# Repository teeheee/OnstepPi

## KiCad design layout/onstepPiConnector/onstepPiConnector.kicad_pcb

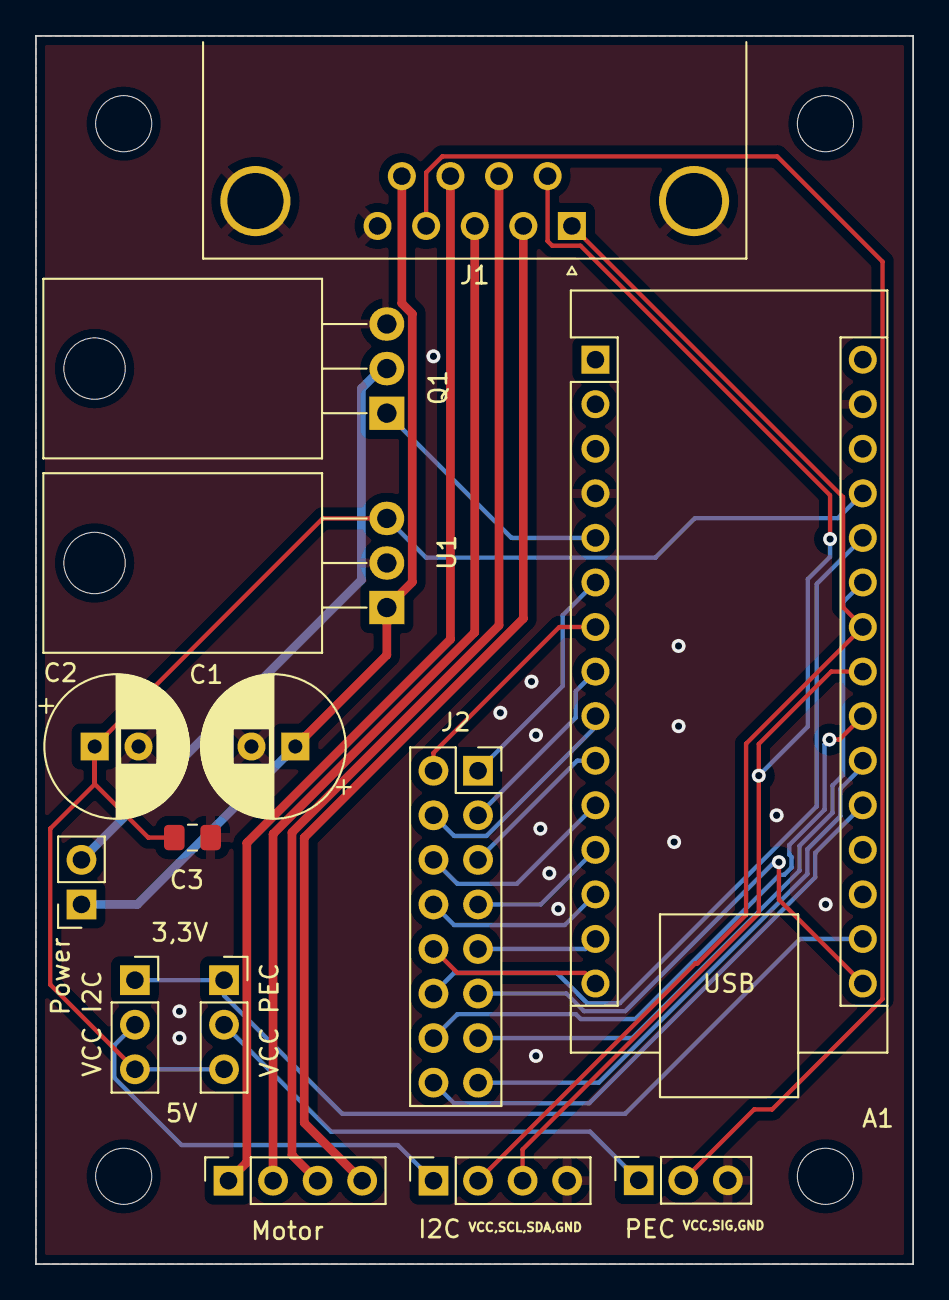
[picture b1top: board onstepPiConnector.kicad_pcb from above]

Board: 2 copper layers, 50.0 x 70.0 mm, 14 parts (0 on the bottom side), 31 nets.

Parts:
A1: Arduino_Nano_v3.x; Arduino_Nano
C1, C2: C_Polarized; CP_Radial_D8.0mm_P2.50mm
C3: C; C_0805_2012Metric_Pad1.18x1.45mm_HandSolder
I2C: Conn_01x04; PinSocket_1x04_P2.54mm_Vertical
J1: DB9_Male_MountingHoles; DSUB-9_Male_Horizontal_P2.77x2.84mm_EdgePinOffset7.70mm_Hou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
J2: Conn_01x16_Male; PinSocket_2x08_P2.54mm_Vertical
Motor: Conn_01x04; PinSocket_1x04_P2.54mm_Vertical
PEC: Conn_01x03; PinSocket_1x03_P2.54mm_Vertical
Power: Conn_01x02; PinSocket_1x02_P2.54mm_Vertical
Q1: IRF540N; TO-220-3_Horizontal_TabDown
U1: L7805; TO-220-3_Horizontal_TabDown
VCC I2C: Jumper_3_Open; PinSocket_1x03_P2.54mm_Vertical
VCC PEC: Jumper_3_Open; PinSocket_1x03_P2.54mm_Vertical

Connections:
+3.3V: A1.17 (3V3), VCC I2C.1 (A), VCC PEC.1 (A)
+5V: A1.27 (+5V), C2.1, C3.1, U1.3 (OUT), VCC I2C.3 (B), VCC PEC.3 (B)
+12V: C1.1, J1.9, Power.1, U1.1 (IN)
GND: A1.4 (GND), A1.29 (GND), C1.2, C2.2, C3.2, I2C.4, J1.0 (PAD), J1.5, PEC.3, Q1.3 (S), U1.2 (GND)
M1A: J1.3, Motor.2
M1B: J1.8, Motor.1
M2A: J1.7, Motor.3
M2B: J1.2, Motor.4
unnamed: A1.5 (D2), Q1.1 (G)
unnamed: A1.6 (D3), J2.1
unnamed: A1.7 (D4), J2.2
unnamed: A1.8 (D5), J2.3
unnamed: A1.9 (D6), J2.4
unnamed: A1.10 (D7), J2.5
unnamed: A1.11 (D8), J2.6
unnamed: A1.12 (D9), J2.7
unnamed: A1.13 (D10), J2.8
unnamed: A1.14 (D11), J2.9
unnamed: A1.15 (D12), J2.10
unnamed: A1.16 (D13), J2.11
unnamed: A1.20 (A1), J2.16
unnamed: A1.21 (A2), J2.15
unnamed: A1.22 (A3), J2.14
unnamed: A1.25 (A6), J2.13
unnamed: A1.26 (A7), J2.12
unnamed: Power.2, Q1.2 (D)
unnamed: I2C.1, VCC I2C.2 (C)
unnamed: PEC.1, VCC PEC.2 (C)
PEC: J1.4, PEC.2
SCL: A1.24 (A5), I2C.2, J1.1
SDA: A1.23 (A4), I2C.3, J1.6

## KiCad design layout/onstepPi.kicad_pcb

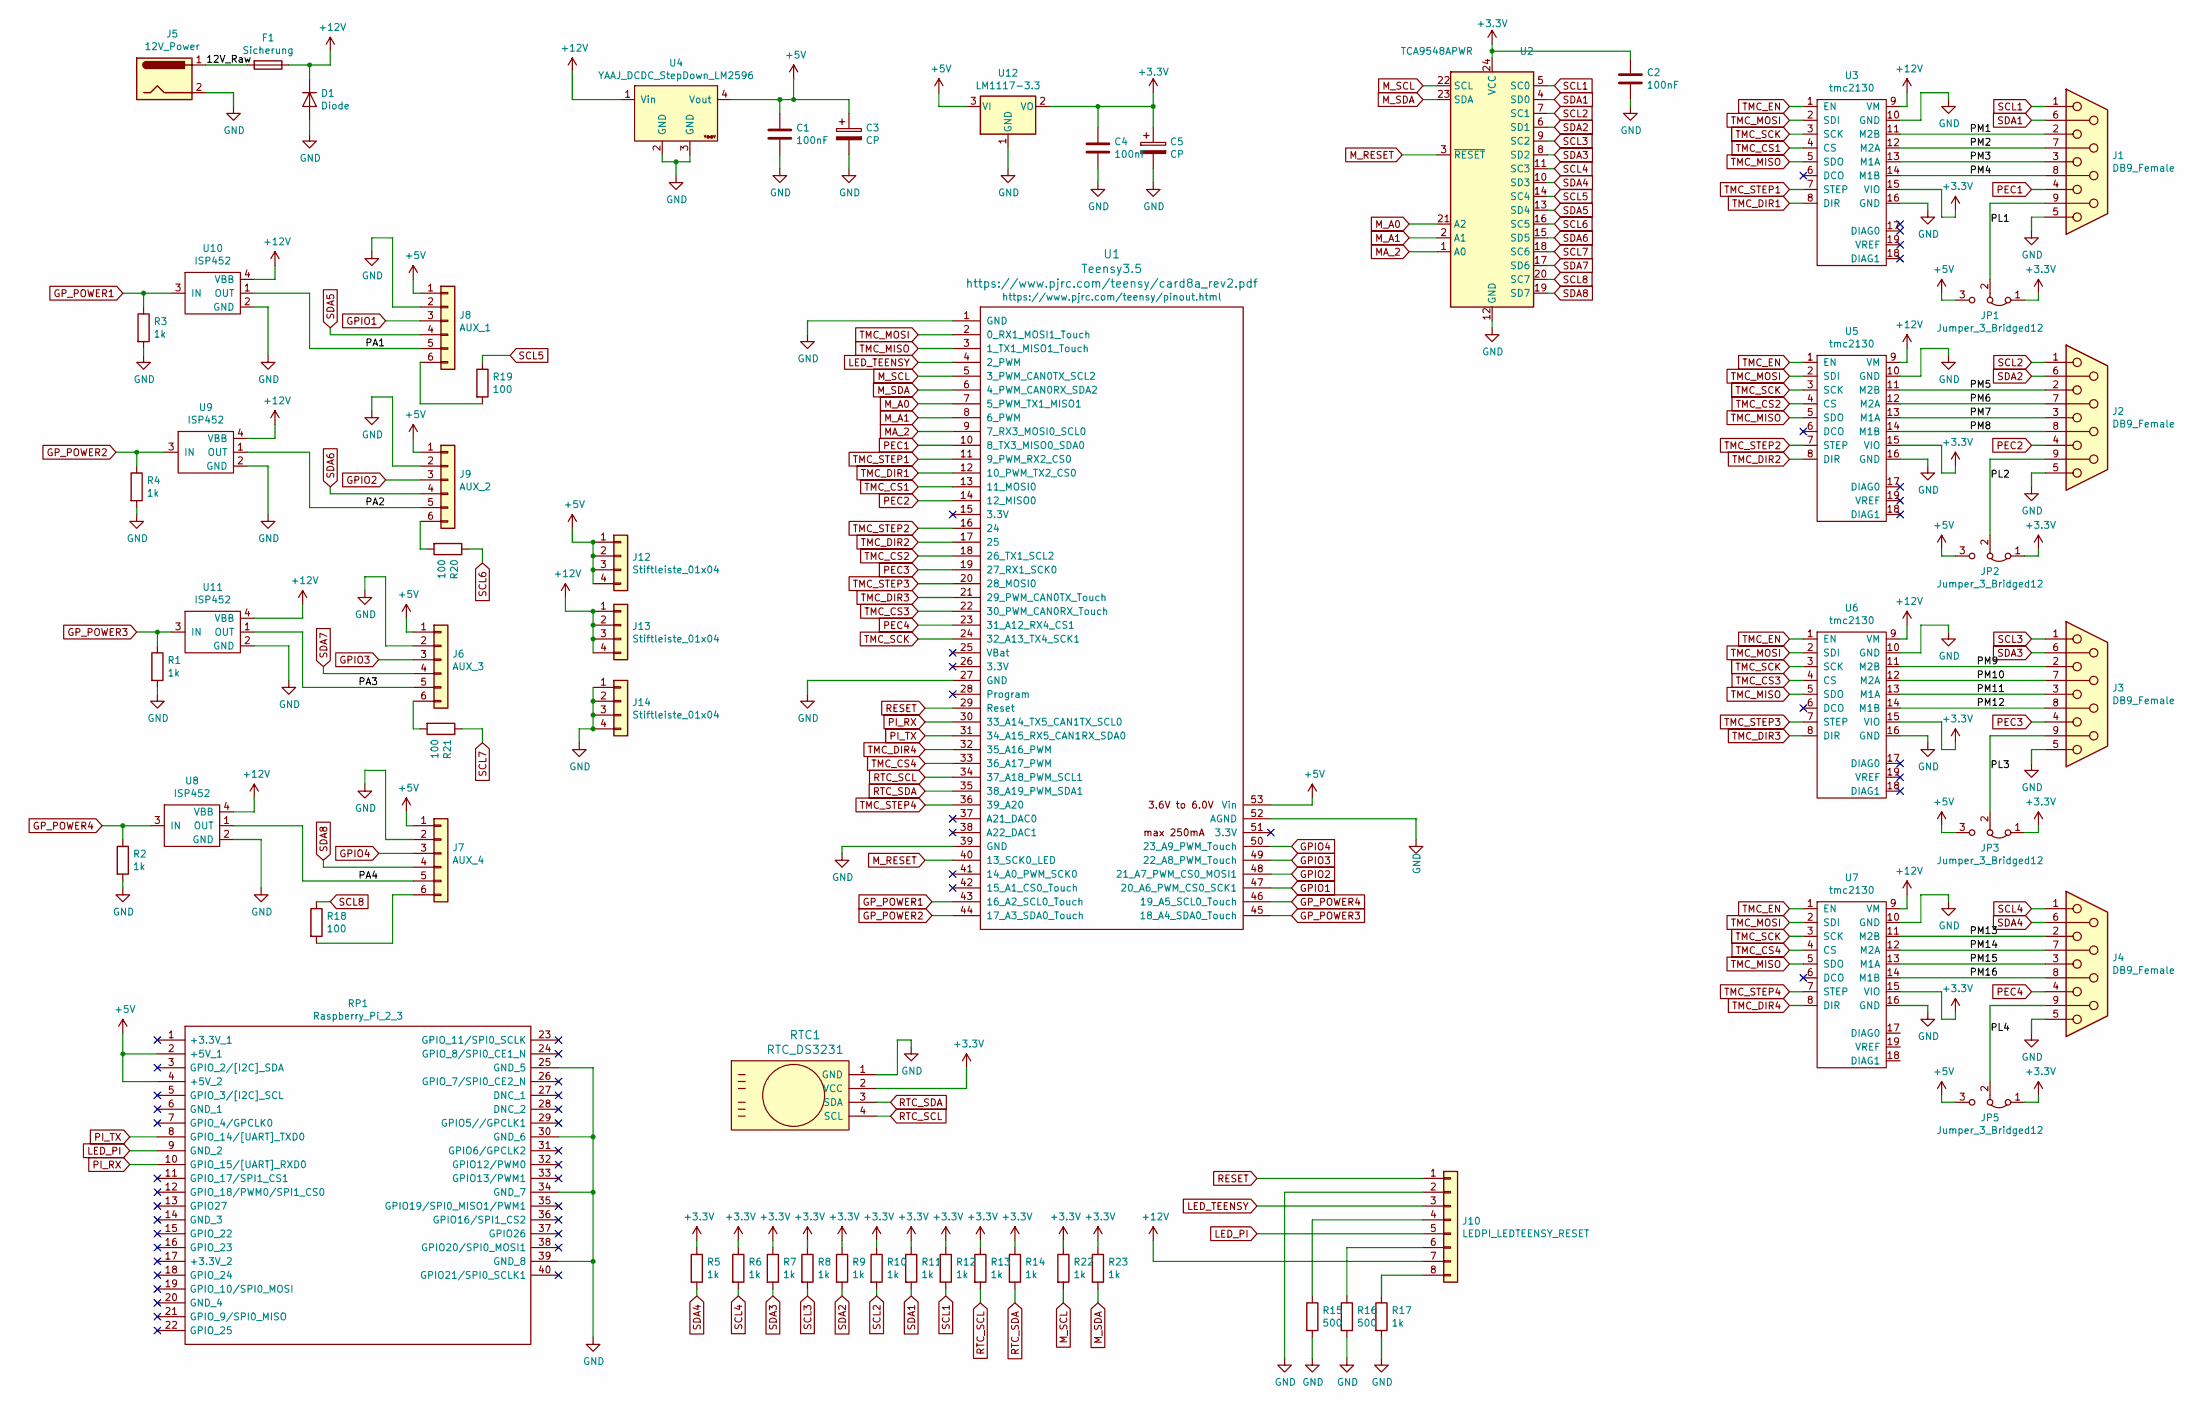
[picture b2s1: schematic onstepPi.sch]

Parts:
C1, C2, C4: 100nF; C_0805_2012Metric_Pad1.18x1.45mm_HandSolder
C3, C5: CP; CP_Radial_D8.0mm_P2.50mm
D1: Diode; D_SMA_Handsoldering
F1: Sicherung; Sicherung_THT
J1, J2, J3, J4: DB9_Female; DSUB-9_Female_Horizontal_P2.77x2.84mm_EdgePinOffset7.70mm_H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
J5: 12V_Power; BarrelJack_Wuerth_6941xx301002
J6: AUX_3; CON_Stiftleiste_6x1
J7: AUX_4; CON_Stiftleiste_6x1
J8: AUX_1; CON_Stiftleiste_6x1
J9: AUX_2; CON_Stiftleiste_6x1
J10: LEDPI_LEDTEENSY_RESET; PinHeader_1x08_P2.54mm_Vertical
J12, J13, J14: Stiftleiste_01x04; CON_Stiftleiste_4x1
JP1, JP2, JP3, JP5: Jumper_3_Bridged12; PinHeader_1x03_P2.54mm_Vertical
R1, R2, R3, R4, R5, R6, R7, R8, R9, R10, R11, R12, R13, R14, R17, R22, R23: 1k; Wiederstand_SMD_0805
R15, R16: 500; Wiederstand_SMD_0805
R18, R19, R20, R21: 100; Wiederstand_SMD_0805
RP1: Raspberry_Pi_2_3; raspberrypi_2_3; Manufacturer_Part_Number Raspberry Pi 2 or 3
RTC1: RTC_DS3231
U1: Teensy3.5; Teensy35_36_All_Pins
U2: TCA9548APWR; TSSOP-24_4.4x7.8mm_P0.65mm
U3, U5, U6, U7: tmc2130
U4: YAAJ_DCDC_StepDown_LM2596
U8, U9, U10, U11: ISP452
U12: LM1117-3.3; TO-263-3_TabPin2

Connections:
+3V3: C2.1, C4.1, C5.1, JP1.1 (A), JP2.1 (A), JP3.1 (A), JP5.1 (A), R5.1, R6.1, R7.1, R8.1, R9.1, R10.1, R11.1, R12.1, R13.1, R14.1, R22.1, R23.1, RTC1.2 (VCC), U2.24 (VCC), U3.15 (VIO), U5.15 (VIO), U6.15 (VIO), U7.15 (VIO), U12.2 (VO)
+5V: C1.1, C3.1, J6.1, J7.1, J8.1, J9.1, J12.1, J12.2, J12.3, J12.4, JP1.3 (B), JP2.3 (B), JP3.3 (B), JP5.3 (B), RP1.2 (+5V_1), RP1.4 (+5V_2), U1.53 (Vin), U4.4 (Vout), U12.3 (VI)
+12V: D1.1 (K), F1.1, J10.7, J13.1, J13.2, J13.3, J13.4, U3.9 (VM), U4.1 (Vin), U5.9 (VM), U6.9 (VM), U7.9 (VM), U8.4 (VBB), U9.4 (VBB), U10.4 (VBB), U11.4 (VBB)
/12V_Raw: F1.2, J5.1
/PA1: J8.5, U10.1 (OUT)
/PA2: J9.5, U9.1 (OUT)
/PA3: J6.5, U11.1 (OUT)
/PA4: J7.5, U8.1 (OUT)
/PL1: J1.9, JP1.2 (C)
/PL2: J2.9, JP2.2 (C)
/PL3: J3.9, JP3.2 (C)
/PL4: J4.9, JP5.2 (C)
/PM1: J1.2, U3.11 (M2B)
/PM2: J1.7, U3.12 (M2A)
/PM3: J1.3, U3.13 (M1A)
/PM4: J1.8, U3.14 (M1B)
/PM5: J2.2, U5.11 (M2B)
/PM6: J2.7, U5.12 (M2A)
/PM7: J2.3, U5.13 (M1A)
/PM8: J2.8, U5.14 (M1B)
/PM9: J3.2, U6.11 (M2B)
/PM10: J3.7, U6.12 (M2A)
/PM11: J3.3, U6.13 (M1A)
/PM12: J3.8, U6.14 (M1B)
/PM13: J4.2, U7.11 (M2B)
/PM14: J4.7, U7.12 (M2A)
/PM15: J4.3, U7.13 (M1A)
/PM16: J4.8, U7.14 (M1B)
GND: C1.2, C2.2, C3.2, C4.2, C5.2, D1.2 (A), J1.5, J2.5, J3.5, J4.5, J5.2, J6.2, J7.2, J8.2, J9.2, J10.2, J14.1, J14.2, J14.3, J14.4, R1.2, R2.2, R3.2, R4.2, R15.2, R16.2, R17.2, RP1.25 (GND_5), RP1.30 (GND_6), RP1.34 (GND_7), RP1.39 (GND_8), RTC1.1 (GND), U1.1 (GND), U1.27 (GND), U1.39 (GND), U1.52 (AGND), U2.12 (GND), U3.10 (GND), U3.16 (GND), U4.2 (GND), U4.3 (GND), U5.10 (GND), U5.16 (GND), U6.10 (GND), U6.16 (GND), U7.10 (GND), U7.16 (GND), U8.2 (GND), U9.2 (GND), U10.2 (GND), U11.2 (GND), U12.1 (GND)
GPIO1: J8.3, U1.47 (20_A6_PWM_CS0_SCK1)
GPIO2: J9.3, U1.48 (21_A7_PWM_CS0_MOSI1)
GPIO3: J6.3, U1.49 (22_A8_PWM_Touch)
GPIO4: J7.3, U1.50 (23_A9_PWM_Touch)
GP_POWER1: R3.1, U1.43 (16_A2_SCL0_Touch), U10.3 (IN)
GP_POWER2: R4.1, U1.44 (17_A3_SDA0_Touch), U9.3 (IN)
GP_POWER3: R1.1, U1.45 (18_A4_SDA0_Touch), U11.3 (IN)
GP_POWER4: R2.1, U1.46 (19_A5_SCL0_Touch), U8.3 (IN)
LED_PI: J10.5, RP1.9 (GND_2)
LED_TEENSY: J10.3, U1.4 (2_PWM)
MA_2: U1.9 (7_RX3_MOSI0_SCL0), U2.1 (A0)
M_A0: U1.7 (5_PWM_TX1_MISO1), U2.21 (A2)
M_A1: U1.8 (6_PWM), U2.2 (A1)
M_RESET: U1.40 (13_SCK0_LED), U2.3 (~RESET)
M_SCL: R22.2, U1.5 (3_PWM_CAN0TX_SCL2), U2.22 (SCL)
M_SDA: R23.2, U1.6 (4_PWM_CAN0RX_SDA2), U2.23 (SDA)
unnamed: J6.6, R21.2
unnamed: J7.6, R18.2
unnamed: J8.6, R19.2
unnamed: J9.6, R20.2
unnamed: J10.4, R15.1
unnamed: J10.6, R16.1
unnamed: J10.8, R17.1
PEC1: J1.4, U1.10 (8_TX3_MISO0_SDA0)
PEC2: J2.4, U1.14 (12_MISO0)
PEC3: J3.4, U1.19 (27_RX1_SCK0)
PEC4: J4.4, U1.23 (31_A12_RX4_CS1)
PI_RX: RP1.10 (GPIO_15/[UART]_RXD0), U1.30 (33_A14_TX5_CAN1TX_SCL0)
PI_TX: RP1.8 (GPIO_14/[UART]_TXD0), U1.31 (34_A15_RX5_CAN1RX_SDA0)
RESET: J10.1, U1.29 (Reset)
RTC_SCL: R13.2, RTC1.4 (SCL), U1.34 (37_A18_PWM_SCL1)
RTC_SDA: R14.2, RTC1.3 (SDA), U1.35 (38_A19_PWM_SDA1)
SCL1: J1.1, R12.2, U2.5 (SC0)
SCL2: J2.1, R10.2, U2.7 (SC1)
SCL3: J3.1, R8.2, U2.9 (SC2)
SCL4: J4.1, R6.2, U2.11 (SC3)
SCL5: R19.1, U2.14 (SC4)
SCL6: R20.1, U2.16 (SC5)
SCL7: R21.1, U2.18 (SC6)
SCL8: R18.1, U2.20 (SC7)
SDA1: J1.6, R11.2, U2.4 (SD0)
SDA2: J2.6, R9.2, U2.6 (SD1)
SDA3: J3.6, R7.2, U2.8 (SD2)
SDA4: J4.6, R5.2, U2.10 (SD3)
SDA5: J8.4, U2.13 (SD4)
SDA6: J9.4, U2.15 (SD5)
SDA7: J6.4, U2.17 (SD6)
SDA8: J7.4, U2.19 (SD7)
TMC_CS1: U1.13 (11_MOSI0), U3.4 (CS)
TMC_CS2: U1.18 (26_TX1_SCL2), U5.4 (CS)
TMC_CS3: U1.22 (30_PWM_CAN0RX_Touch), U6.4 (CS)
TMC_CS4: U1.33 (36_A17_PWM), U7.4 (CS)
TMC_DIR1: U1.12 (10_PWM_TX2_CS0), U3.8 (DIR)
TMC_DIR2: U1.17 (25), U5.8 (DIR)
TMC_DIR3: U1.21 (29_PWM_CAN0TX_Touch), U6.8 (DIR)
TMC_DIR4: U1.32 (35_A16_PWM), U7.8 (DIR)
TMC_EN: U3.1 (EN), U5.1 (EN), U6.1 (EN), U7.1 (EN)
TMC_MISO: U1.3 (1_TX1_MISO1_Touch), U3.5 (SDO), U5.5 (SDO), U6.5 (SDO), U7.5 (SDO)
TMC_MOSI: U1.2 (0_RX1_MOSI1_Touch), U3.2 (SDI), U5.2 (SDI), U6.2 (SDI), U7.2 (SDI)
TMC_SCK: U1.24 (32_A13_TX4_SCK1), U3.3 (SCK), U5.3 (SCK), U6.3 (SCK), U7.3 (SCK)
TMC_STEP1: U1.11 (9_PWM_RX2_CS0), U3.7 (STEP)
TMC_STEP2: U1.16 (24), U5.7 (STEP)
TMC_STEP3: U1.20 (28_MOSI0), U6.7 (STEP)
TMC_STEP4: U1.36 (39_A20), U7.7 (STEP)

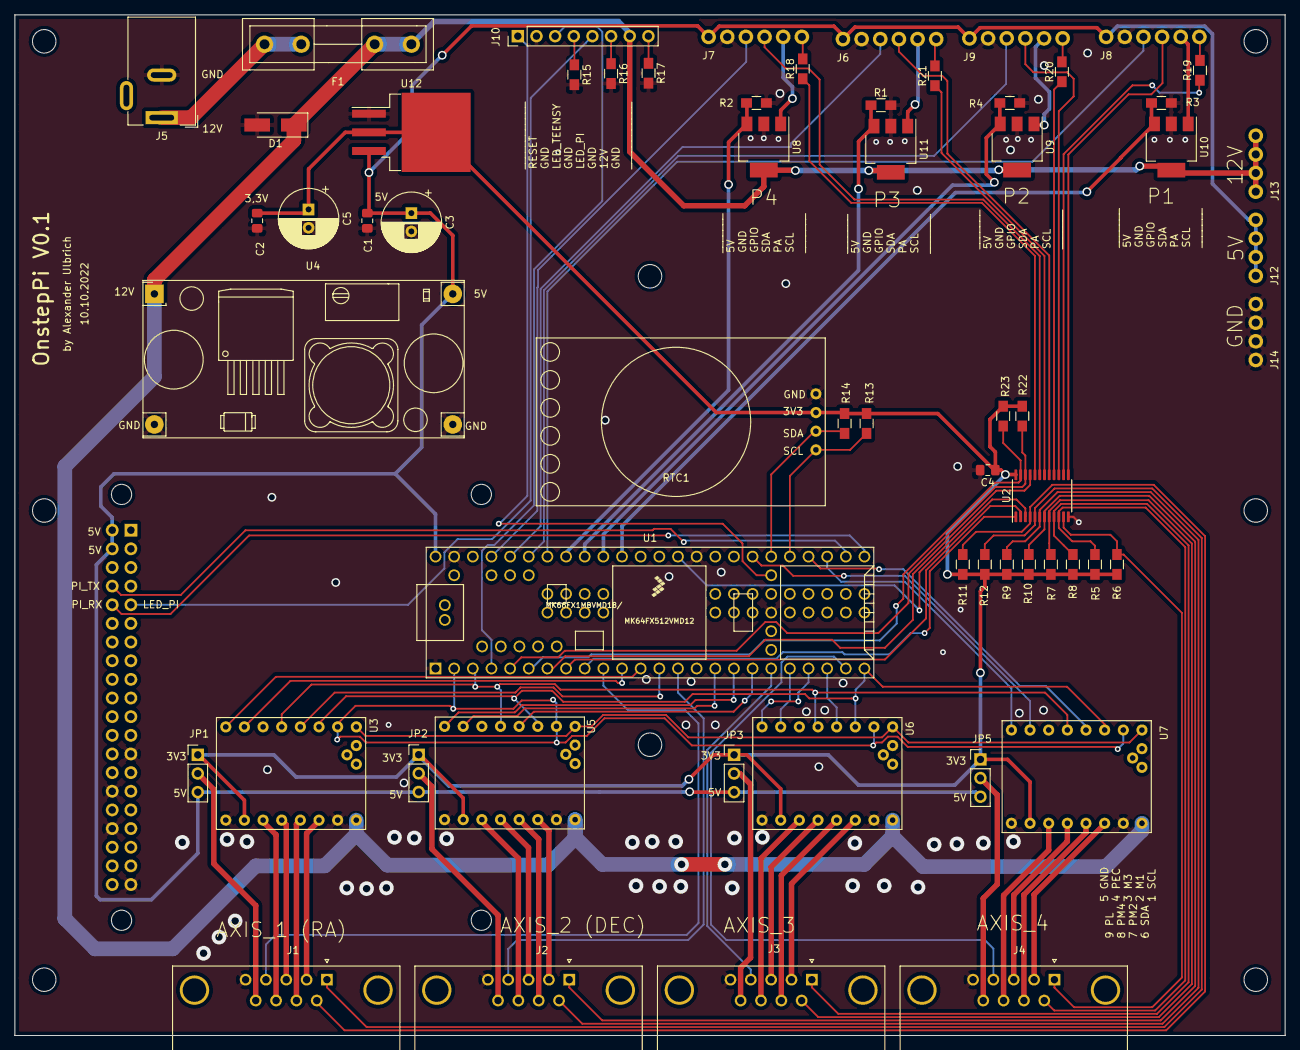
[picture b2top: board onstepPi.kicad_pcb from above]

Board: 2 copper layers, 173.0 x 139.0 mm, 61 parts (1 on the bottom side), 93 nets.

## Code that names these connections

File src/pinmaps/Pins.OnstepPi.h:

// -------------------------------------------------------------------------------------------------
// Pin map for OnStepPi (Teensy3.5/3.6)
#pragma once

#if defined(__MK64FX512__) || defined(__MK66FX1M0__)

// Serial ports (see Pins.defaults.h for SERIAL_A)
// Serial1: RX1 Pin 0, TX1 Pin 1
// Serial4: RX4 Pin 31, TX4 Pin 32

#if SERIAL_A_BAUD_DEFAULT != OFF
  #define SERIAL_A              Serial5
#endif
#if SERIAL_B_BAUD_DEFAULT != OFF
  #define SERIAL_B              Serial1
#endif
#if SERIAL_C_BAUD_DEFAULT != OFF
  #define SERIAL_C              Serial4
#endif
#if defined(USB_DUAL_SERIAL) || defined(USB_TRIPLE_SERIAL)
  #define SERIAL_D              SerialUSB1
  #define SERIAL_D_BAUD_DEFAULT 9600
#endif
#if defined(USB_TRIPLE_SERIAL)
  #define SERIAL_E              SerialUSB2
  #define SERIAL_E_BAUD_DEFAULT 9600
#endif

// The multi-purpose pins (Aux3..Aux8 can be analog pwm/dac if supported)
#define AUX0_PIN               2                // Status LED
#define AUX1_PIN               OFF              // ESP8266 GPIO0, SPI MISO/Fault
#define AUX2_PIN               OFF               // ESP8266 RST, SPI MISO/Fault
#define AUX3_PIN               OFF              // Home SW
#define AUX4_PIN               OFF              // OneWire, Home SW
#define AUX5_PIN               OFF                // AXIS3_EN_PIN; true analog output
#define AUX6_PIN               OFF               // AXIS4_EN_PIN; true analog output
#define AUX7_PIN               OFF                   // Limit SW
#define AUX8_PIN               OFF                // Status2 LED, Reticle LED

// Misc. pins
#ifndef DS3234_CS_PIN
  #define DS3234_CS_PIN        OFF                // Default CS Pin for DS3234 on SPI
#endif
#ifndef ONE_WIRE_PIN
  #define ONE_WIRE_PIN         AUX4_PIN          // Default Pin for OneWire bus (note: this pin has a 0.1uF capacitor that must be removed for OneWire to function)
#endif
#define ADDON_GPIO0_PIN        AUX1_PIN          // ESP8266 GPIO0 or SPI MISO/Fault
#define ADDON_RESET_PIN        AUX2_PIN          // ESP8266 RST or SPI MISO/Fault

// The PEC index sense is a logic level input, resets the PEC index on rising edge then waits for 60 seconds before allowing another reset
#ifndef PEC_SENSE_PIN
  #define PEC_SENSE_PIN        OFF                // PEC Sense, analog or digital
#endif

// The status LED is a two wire jumper with a 10k resistor in series to limit the current to the LED
#define STATUS_LED_PIN         2          // LED Anode (+)
#define STATUS_LED_ON_STATE    HIGH             // LED Anode (+)

#define MOUNT_STATUS_LED_PIN   AUX0_PIN          // Default LED Cathode (-)
#ifndef RETICLE_LED_PIN
  #define RETICLE_LED_PIN      AUX8_PIN          // Default LED Cathode (-)
#endif

// For a piezo buzzer
#define STATUS_BUZZER_PIN      OFF                // Tone

// The PPS pin is a 3.3V logic input, OnStep measures time between rising edges and adjusts the internal sidereal clock frequency
#ifndef PPS_SENSE_PIN
  #define PPS_SENSE_PIN        OFF                // PPS time source, GPS for example
#endif

#ifndef LIMIT_SENSE_PIN
  #define LIMIT_SENSE_PIN      AUX7_PIN          // The limit switch sense is a logic level input normally pull high (2k resistor,) shorted to ground it stops gotos/tracking
#endif

#define TMC_MOSI    0
#define TMC_MISO    1
#define TMC_SCK     32
#define TMC_ENABLE  14

#define SHARED_ENABLE_PIN TMC_ENABLE

// Axis1 RA/Azm step/dir driver
#define AXIS1_ENABLE_PIN       SHARED
#define AXIS1_M0_PIN           TMC_MOSI          // SPI MOSI
#define AXIS1_M1_PIN           TMC_SCK           // SPI SCK
#define AXIS1_M2_PIN           11                // SPI CS (UART TX)
#define AXIS1_M3_PIN           TMC_MISO          // SPI MISO (UART RX)
#define AXIS1_STEP_PIN         9
#define AXIS1_DIR_PIN          10
#define AXIS1_DECAY_PIN        OFF
#define AXIS1_FAULT_PIN        OFF
#ifndef AXIS1_SENSE_HOME_PIN
  #define AXIS1_SENSE_HOME_PIN OFF
#endif
#define AXIS1_ENCODER_A_PIN    OFF
#define AXIS1_ENCODER_B_PIN    OFF
#define AXIS1_SERVO_PH1_PIN    OFF
#define AXIS1_SERVO_PH2_PIN    OFF

// Axis2 Dec/Alt step/dir driver
#define AXIS2_ENABLE_PIN       SHARED
#define AXIS2_M0_PIN           TMC_MOSI                 // SPI MOSI
#define AXIS2_M1_PIN           TMC_SCK                 // SPI SCK
#define AXIS2_M2_PIN           26                 // SPI CS (UART TX)
#define AXIS2_M3_PIN           TMC_MISO          // SPI MISO (UART RX)
#define AXIS2_STEP_PIN         24
#define AXIS2_DIR_PIN          25
#define AXIS2_DECAY_PIN        OFF
#define AXIS2_FAULT_PIN        OFF
#ifndef AXIS2_SENSE_HOME_PIN
  #define AXIS2_SENSE_HOME_PIN OFF
#endif
#define AXIS2_ENCODER_A_PIN    OFF
#define AXIS2_ENCODER_B_PIN    OFF
#define AXIS2_SERVO_PH1_PIN    OFF
#define AXIS2_SERVO_PH2_PIN    OFF

// For rotator stepper driver
#define AXIS3_ENABLE_PIN       OFF
#define AXIS3_M0_PIN           OFF               // SPI MOSI
#define AXIS3_M1_PIN           OFF               // SPI SCK
#define AXIS3_M2_PIN           OFF               // SPI CS
#define AXIS3_M3_PIN           OFF               // SPI MISO
#define AXIS3_STEP_PIN         OFF
#define AXIS3_DIR_PIN          OFF

// For focuser1 stepper driver
#define AXIS4_ENABLE_PIN       SHARED
#define AXIS4_M0_PIN           OFF               // SPI MOSI
#define AXIS4_M1_PIN           OFF               // SPI SCK
#define AXIS4_M2_PIN           OFF               // SPI CS
#define AXIS4_M3_PIN           OFF               // SPI MISO
#define AXIS4_STEP_PIN         28 
#define AXIS4_DIR_PIN          29

// For focuser2 stepper driver
#define AXIS5_ENABLE_PIN       SHARED
#define AXIS5_M0_PIN           OFF               // SPI MOSI
#define AXIS5_M1_PIN           OFF               // SPI SCK
#define AXIS5_M2_PIN           OFF               // SPI CS
#define AXIS5_M3_PIN           OFF               // SPI MISO
#define AXIS5_STEP_PIN         39
#define AXIS5_DIR_PIN          35
#define AXIS5_SENSE_HOME_PIN   31

// ST4 interface
#define ST4_RA_W_PIN           OFF                // ST4 RA- West
#define ST4_DEC_S_PIN          OFF                // ST4 DE- South
#define ST4_DEC_N_PIN          OFF                // ST4 DE+ North
#define ST4_RA_E_PIN           OFF                // ST4 RA+ East

#else
#error "Wrong processor for this configuration!"

#endif

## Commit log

2023-04-22 increase SoftSPI delay
2023-04-22 add OnstepPi pin config
2023-04-22 add build for platformio
2023-04-22 add layout files
2023-04-23 added focuser update
2023-04-23 bugfix
2023-05-27 update config
2023-05-28 increase RA current
